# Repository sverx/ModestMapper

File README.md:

# the ModestMapper

the ModestMapper is an open _low-cost_ **rewritable** cartridge for the SEGA Master System.

It's based on [doragasu's FrugalMapper cartridge](https://gitlab.com/doragasu/sms-sl2map) and shares many of its features:

- uses a Flash memory chip instead of ROM chips, thus being rewritable
- uses only discrete logic chips, as few of them as possible
- can be programmed and reprogrammed after having being assembled
- supports up to 4 Mbit (512 KiB) but can use 2 Mbit (256 KiB) and 1 Mbit (128 KiB) Flash chips too (currently _untested_ but the design allows for that)

While doragasu's FrugalMapper supports slot-2 SEGA mapper only, the ModestMapper supports both slot-1 **and** slot-2 SEGA mapper, making it perfect for [devkitSMS](https://github.com/sverx/devkitSMS) games that use [transparent code bankswitching](https://github.com/sverx/devkitSMS#advanced-how-to-use-more-than-32-kib-of-code-in-your-smsggsgsc-rom-banked-code) for example, but can be used for any game requiring slot-1 and slot-2 paging (please read the note on the _Words of caution_ section below).

# How it works

the ModestMapper implements only a subset of the complete [SEGA mapper](https://www.smspower.org/Development/Mappers#TheSegaMapper) specifications so:

- slot-0 paging isn't supported, thus the first 16 KiB of the data in the ROM will always be accessible at address $0000-$3FFF
- slot-1 and slot-2 paging **are** supported, thus any of the 16 KiB blocks of the ROM can be accessible at addresses $4000-$7FFF (slot-1) and $8000-$BFFF (slot-2)
- up to 32 × 16-KiB ROM pages are supported
- advanced SEGA mapper features such as bankshifting or write protection aren't supported

# Words of caution

Since address decoding is partial, any writes to addresses $E000-$FFFF (RAM _mirror_ addresses) will work as writes to the SEGA mapper ports $FFFC-$FFFF - see the following table:

       writes to                              |     effect
    ------------------------------------------+----------------------
    %111x xxxx xxxx xx00 ($FFFC and mirrors)  |   _none_ (ignored)
    %111x xxxx xxxx xx01 ($FFFD and mirrors)  |   _none_ (ignored)
    %111x xxxx xxxx xx10 ($FFFE and mirrors)  |   **set slot-1 page**
    %111x xxxx xxxx xx11 ($FFFF and mirrors)  |   **set slot-2 page**

This shouldn't cause any issues provided that the program **never** writes to RAM _mirror_ addresses ([Emulicious](https://emulicious.net)' debugger has a very useful feature to detect if this happens).

Also of note is that the slot-1 and slot-2 pages are **NOT** initialized by the hardware so the [SEGA signature](https://www.smspower.org/Development/ROMHeader) that's **required** by the Master System BIOS to be in the ROM at a certain locations **can't** be located at $7FF0 but **has** to be located at $3FF0 instead (devkitSMS has a macro for that: *SMS_EMBED_SEGA_ROM_HEADER_16KB*) - or at $1FF0.

# How to write a ROM onto the cartridge

You can use either [Raphnet's SMS cartridge reader/programmer](https://www.raphnet-tech.com/products/sms_cartridge_reader_programmer/index.php) with an [updated firmware](https://github.com/sverx/smscprogr) (tested personally) or you can use [doragasu's MegaWiFi programmer](https://gitlab.com/doragasu/mw-prog) (not tested yet but it should work as the ModestMapper is compatible with the FrugalMapper by design).

# License

the ModestMapper cartridge design is Open Hardware, licensed under the CERN-OHL-S license, as it's a  derivate work of [doragasu's FrugalMapper cartridge](https://gitlab.com/doragasu/sms-sl2map)

# Acknowledgements

This project wouldn't have ever been possible without doragasu's FrugalMapper and doragasu's invaluable help while designing this. Also a big THANK YOU to the [SMS Power!](https://www.smspower.org) community and in particolar to @undeveloper ❤️

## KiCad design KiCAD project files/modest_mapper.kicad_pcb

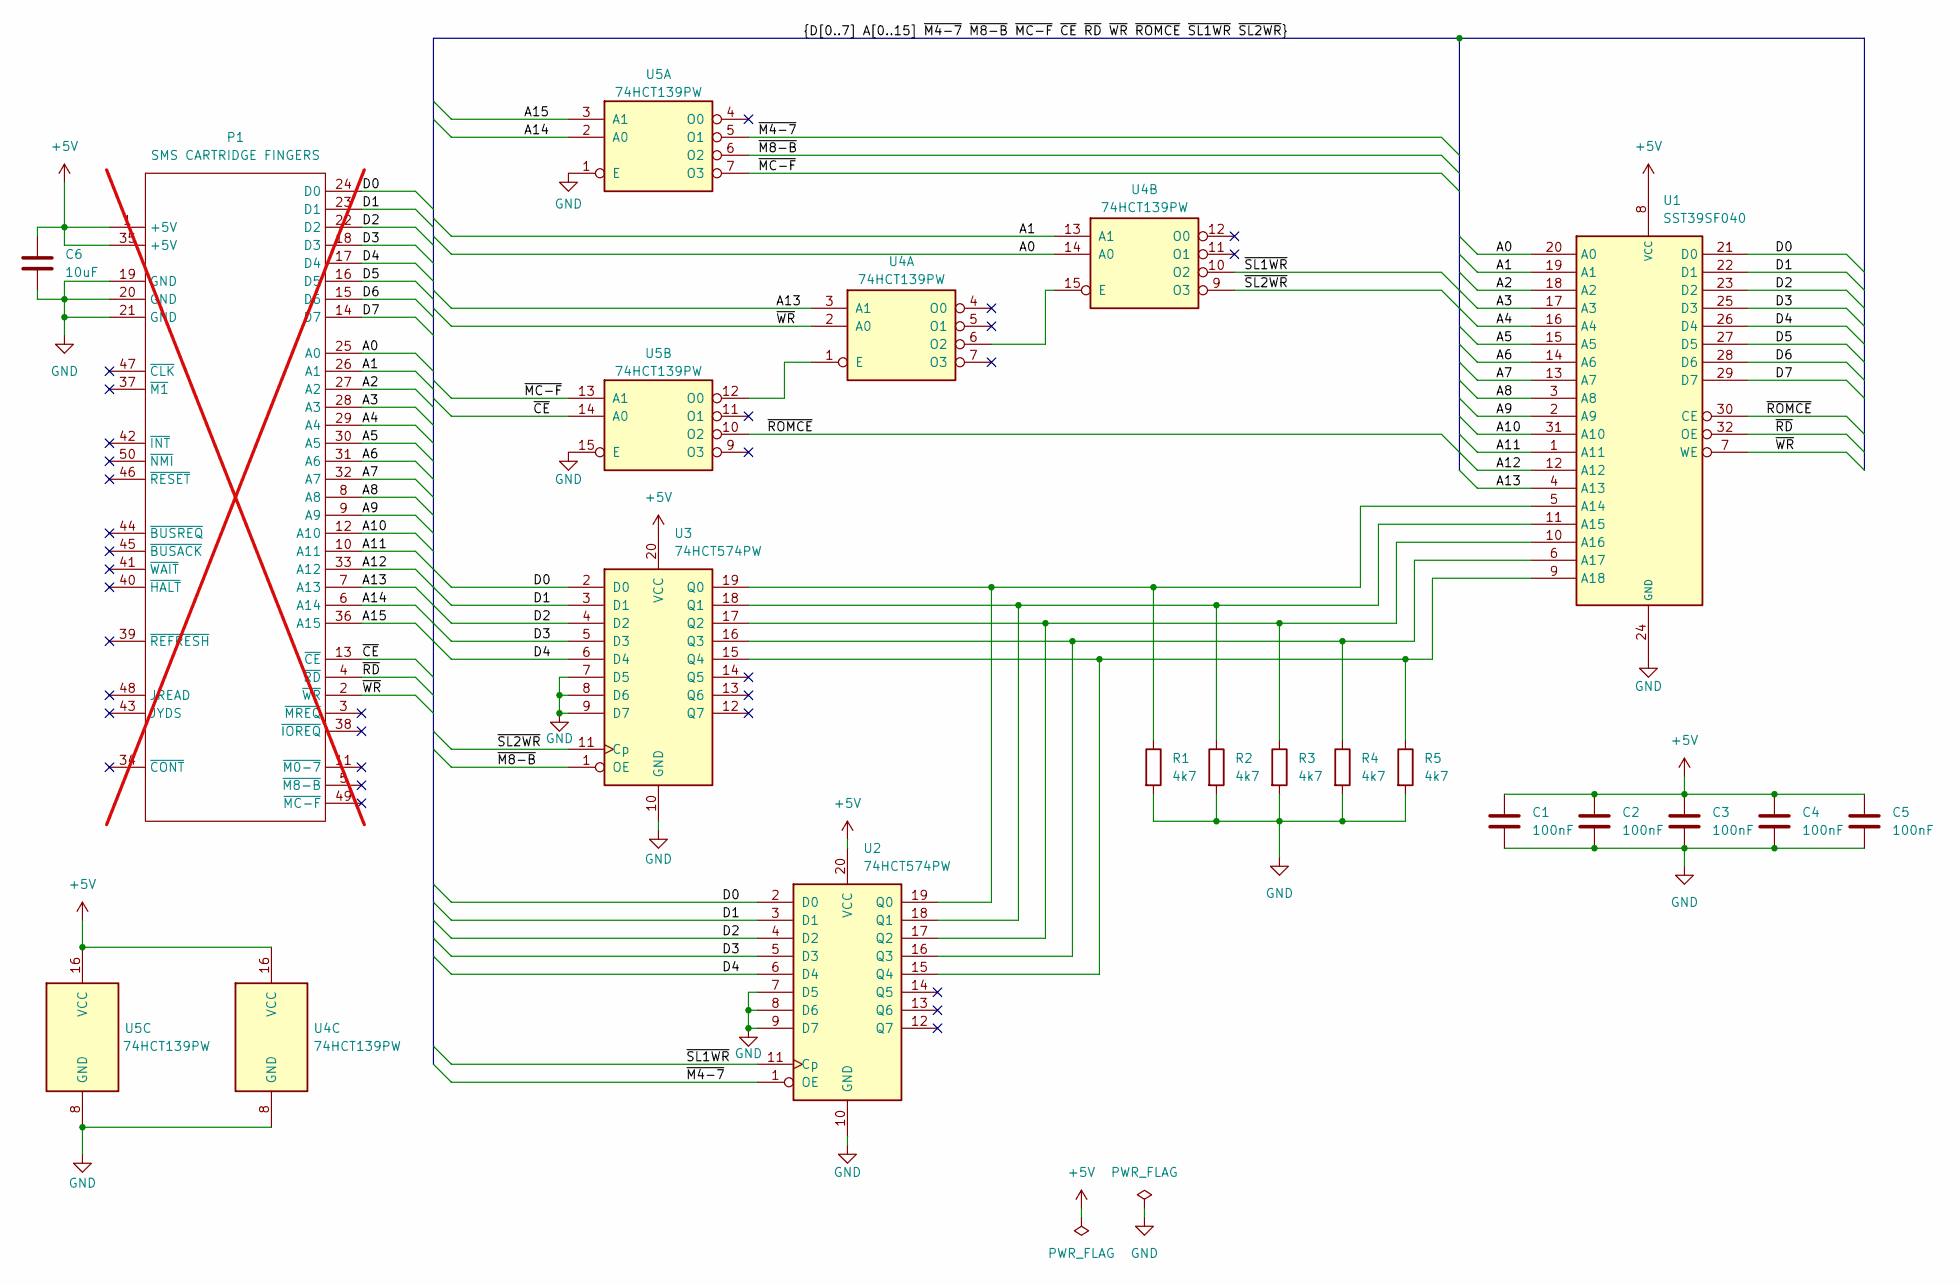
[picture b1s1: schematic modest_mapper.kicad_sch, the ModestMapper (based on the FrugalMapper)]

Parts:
C1, C2, C3, C4, C5: 100nF; C_0603_1608Metric
C6: 10uF; C_0805_2012Metric
P1: SMS CARTRIDGE FINGERS; not fitted
R1, R2, R3, R4, R5: 4k7; R_0603_1608Metric
U1: SST39SF040; TSOP-I-32_11.8x8mm_P0.5mm
U2, U3: 74HCT574PW; TSSOP-20_4.4x6.5mm_P0.65mm
U4, U5: 74HCT139PW; TSSOP-16_4.4x5mm_P0.65mm

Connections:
+5V: C1.1, C2.1, C3.1, C4.1, C5.1, C6.1, P1.1 (+5V), P1.35 (+5V), U1.8 (VCC), U2.20 (VCC), U3.20 (VCC), U4.16 (VCC), U5.16 (VCC)
/A0: P1.25 (A0), U1.20 (A0), U4.14 (A0)
/A1: P1.26 (A1), U1.19 (A1), U4.13 (A1)
/A2: P1.27 (A2), U1.18 (A2)
/A3: P1.28 (A3), U1.17 (A3)
/A4: P1.29 (A4), U1.16 (A4)
/A5: P1.30 (A5), U1.15 (A5)
/A6: P1.31 (A6), U1.14 (A6)
/A7: P1.32 (A7), U1.13 (A7)
/A8: P1.8 (A8), U1.3 (A8)
/A9: P1.9 (A9), U1.2 (A9)
/A10: P1.12 (A10), U1.31 (A10)
/A11: P1.10 (A11), U1.1 (A11)
/A12: P1.33 (A12), U1.12 (A12)
/A13: P1.7 (A13), U1.4 (A13), U4.3 (A1)
/A14: P1.6 (A14), U5.2 (A0)
/A15: P1.36 (A15), U5.3 (A1)
/D0: P1.24 (D0), U1.21 (D0), U2.2 (D0), U3.2 (D0)
/D1: P1.23 (D1), U1.22 (D1), U2.3 (D1), U3.3 (D1)
/D2: P1.22 (D2), U1.23 (D2), U2.4 (D2), U3.4 (D2)
/D3: P1.18 (D3), U1.25 (D3), U2.5 (D3), U3.5 (D3)
/D4: P1.17 (D4), U1.26 (D4), U2.6 (D4), U3.6 (D4)
/D5: P1.16 (D5), U1.27 (D5)
/D6: P1.15 (D6), U1.28 (D6)
/D7: P1.14 (D7), U1.29 (D7)
/~CE: P1.13 (~CE), U5.14 (A0)
/~M4-7: U2.1 (OE), U5.5 (O1)
/~M8-B: U3.1 (OE), U5.6 (O2)
/~MC-F: U5.7 (O3), U5.13 (A1)
/~RD: P1.4 (~RD), U1.32 (OE)
/~ROMCE: U1.30 (CE), U5.10 (O2)
/~SL1WR: U2.11 (Cp), U4.10 (O2)
/~SL2WR: U3.11 (Cp), U4.9 (O3)
/~WR: P1.2 (~WR), U1.7 (WE), U4.2 (A0)
GND: C1.2, C2.2, C3.2, C4.2, C5.2, C6.2, P1.19 (GND), P1.20 (GND), P1.21 (GND), R1.2, R2.2, R3.2, R4.2, R5.2, U1.24 (GND), U2.7 (D5), U2.8 (D6), U2.9 (D7), U2.10 (GND), U3.7 (D5), U3.8 (D6), U3.9 (D7), U3.10 (GND), U4.8 (GND), U5.1 (E), U5.8 (GND), U5.15 (E)
unnamed: R1.1, U1.5 (A14), U2.19 (Q0), U3.19 (Q0)
unnamed: R2.1, U1.11 (A15), U2.18 (Q1), U3.18 (Q1)
unnamed: R3.1, U1.10 (A16), U2.17 (Q2), U3.17 (Q2)
unnamed: R4.1, U1.6 (A17), U2.16 (Q3), U3.16 (Q3)
unnamed: R5.1, U1.9 (A18), U2.15 (Q4), U3.15 (Q4)
unnamed: U4.1 (E), U5.12 (O0)
unnamed: U4.6 (O2), U4.15 (E)

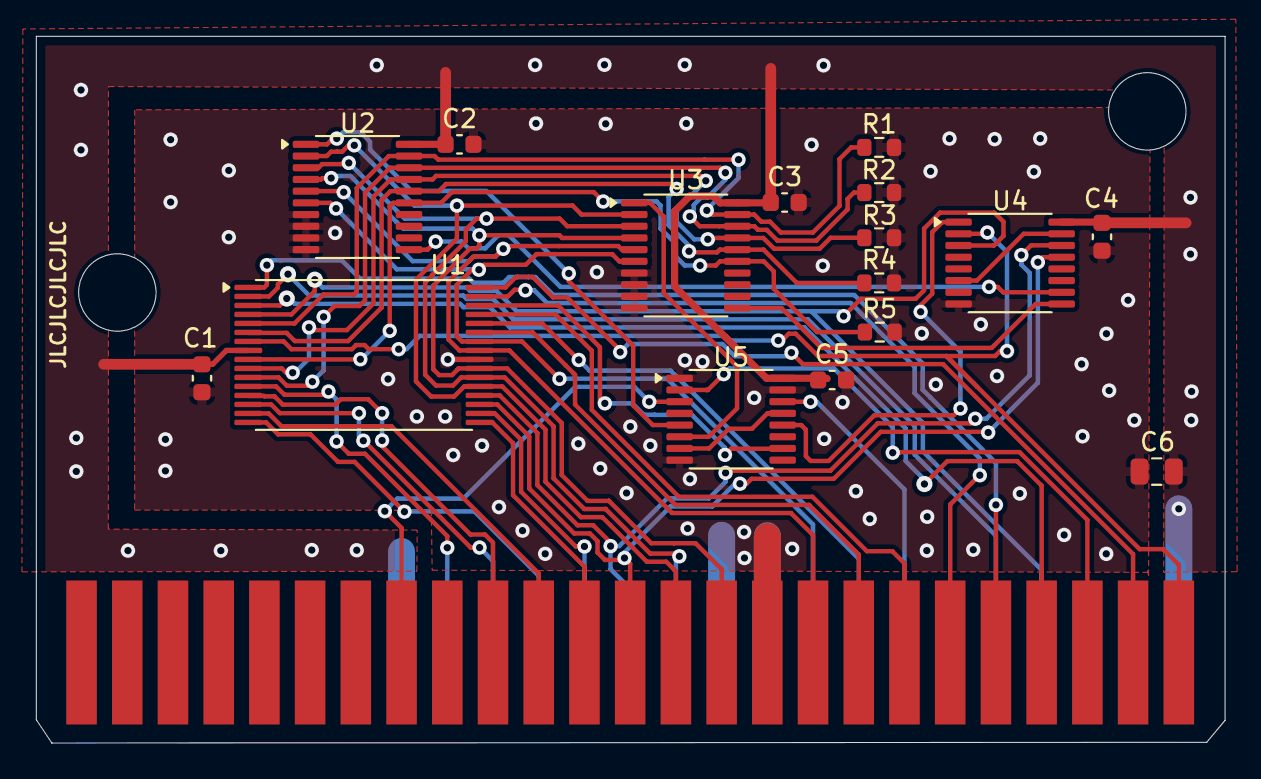
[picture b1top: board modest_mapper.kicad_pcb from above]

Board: 4 copper layers, 66.0 x 39.3 mm, 17 parts (0 on the bottom side), 42 nets.

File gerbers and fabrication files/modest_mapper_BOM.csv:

"Id";"Designator";"Footprint";"Quantity";"Designation";"Supplier and ref";
1;"C2,C3,C1,C4,C5";"C_0603_1608Metric";5;"100nF";;;
2;"R1,R5,R4,R2,R3";"R_0603_1608Metric";5;"4k7";;;
3;"U5,U4";"TSSOP-16_4.4x5mm_P0.65mm";2;"74HCT139PW";;;
4;"U1";"TSOP-I-32_11.8x8mm_P0.5mm";1;"SST39SF040";;;
5;"C6";"C_0805_2012Metric";1;"10uF";;;
6;"U2,U3";"TSSOP-20_4.4x6.5mm_P0.65mm";2;"74HCT574PW";;;

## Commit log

2026-05-19 first release
